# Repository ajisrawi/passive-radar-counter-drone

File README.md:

A **passive radar** that finds small drones without transmitting anything. It listens to the **digital TV, 4G and 5G signals already in the air**. It compares each signal as it arrives straight from the tower with its faint echo off a drone, which gives range, speed and bearing. An on-board FPGA then tells **drones from birds** by their micro-Doppler: spinning rotors make different echo patterns from flapping wings.

- **No transmitter:** no licence needed, nothing to jam, and the radar itself is invisible.
- **Three illuminators at once:** TV towers give long range, and wide 4G/5G channels give fine range resolution.
- **Built end to end:** simulation → custom PCBs → FPGA firmware → antennas → radome → enclosure.

<p align="center">
  
  <br><sub><b>The whole site:</b> one antenna radome (all four bands), two reference antennas pointing at the transmitters, one receiver box</sub>
</p>

---

## Contents

- [How it works](#how-it-works)
- [Simulation results](#simulation-results)
- [Receiver hardware](#receiver-hardware)
- [Firmware: FPGA + ARM](#firmware-fpga--arm)
- [Antennas and radome](#antennas-and-radome)
- [Enclosure](#enclosure)
- [Run it](#run-it)
- [Repository layout](#repository-layout)
- [Status](#status)

---

## How it works

```
   TV / 4G / 5G tower ──────── direct signal ───────────►  reference antenna (LPDA) ─┐
          │                                                                          │
          └──► drone ── faint echo ──►  surveillance array (4 slant dipoles / band) ──┤
                                                                                     ▼
   Board A2  RF front end, 6 ch, LNAs + noise-source calibration (one per band)
        │
   Board B   3 × AD9361 digitizer, 6 coherent channels            ×2 stacks per band
        │
   Board C2  Zynq: cancel the direct signal ─► stream to host ─► detect, track
             └► micro-Doppler engine (8 cued targets) ─► ARM classifier: UAV / bird
```

| Band group | Frequencies | Services | Why |
|---|---|---|---|
| `uhf` | 470–821 MHz | DVB-T, LTE B20/B28, 5G n28 | high-power TV towers give the longest range |
| `mid` | 1805–2170 MHz | LTE B3, B1 | dense cell coverage |
| `high` | 2496–2690 MHz | LTE B7, 5G n41 | wide channels |
| `n78` | 3300–3800 MHz | 5G n78 | 100 MHz channels give the finest range resolution |

The full design, from requirements to link budget, architecture and deployment, is in **[docs/DESIGN.md](docs/DESIGN.md)**.

---

## Simulation results

A Python model of the whole signal-processing chain (`pcl/`) puts a quadcopter, a fixed-wing drone and a bird in a simulated scene.

<p align="center">
  
  <br><sub><b>Range-Doppler map.</b> Left: the direct signal and ground clutter hide everything. Right: after clutter cancellation (ECA) and beamforming, both drones stand out about 25 dB above the noise.</sub>
</p>

<p align="center">
  
  <br><sub><b>Micro-Doppler.</b> The bird's wing beat hugs the body line. The drones show rotor or propeller lines out to ±240 Hz, so they're classified as <b>UAV</b>.</sub>
</p>

<table>
<tr>
<td width="50%"><br><sub><b>Tracking:</b> an EKF tracker over 10 s. Each track is labelled bird or UAV.</sub></td>
<td width="50%"><br><sub><b>Localisation:</b> the bistatic range ellipse crossed with the measured direction of arrival.</sub></td>
</tr>
</table>

---

## Receiver hardware

There are three custom boards per receiver stack, all designed in **OpenSchematic / OpenBoard**. Each band has one A2 front end and two stacks.

<table>
<tr>
<td width="50%"></td>
<td width="50%"></td>
</tr>
<tr>
<td><b>Board C2:</b> Zynq XC7Z035, DDR3, SFP+ 10 GbE, FMC to Board B. 10 layers, 0 DRC errors.</td>
<td><b>Board B:</b> three AD9361 transceivers giving 6 phase-coherent receive channels, with a shared clock and multi-chip sync.</td>
</tr>
<tr>
<td width="50%"></td>
<td width="50%"></td>
</tr>
<tr>
<td><b>Board A2:</b> six-channel RF front end with LNAs, band filters and a noise source that calibrates all channels' phase. Built in four band versions.</td>
<td><b>Board C:</b> Zynq XC7Z020, the lower-cost processor for TV-only stacks.</td>
</tr>
</table>

Schematics, layouts, Gerbers, BOMs and pick-and-place files are in `hardware/board_*/` and `hardware/release/`. See **[hardware/HARDWARE.md](hardware/HARDWARE.md)**.

---

## Firmware: FPGA + ARM

| Block | What it does | Verified |
|---|---|---|
| `canceller.v` | 128-tap complex direct-signal canceller per channel; taps loaded from the host | bit-exact against the Python model, 0 mismatches |
| `md_engine.v` | micro-Doppler engine: beamforms and range-gates up to 8 targets the host is tracking, continuously | 0 mismatches |
| `stream_pack.v` | packs reference + residual into UDP-sized packets | 0 mismatches |
| `ad_merge.v` | aligns the three AD9361 clock domains | 955 samples aligned, no loss |
| `md_classifier.py` (ARM) | Hann spectra → UAV / bird / no signal | false-alarm rate 0.25% |

**End-to-end simulation:** a near quadcopter is classified **UAV** in 4 s and a bird **bird**; the canceller removes 43.6 dB of direct signal. The Board C build uses 67% of the XC7Z020's DSP slices. Details are in **[firmware/FIRMWARE.md](firmware/FIRMWARE.md)**.

---

## Antennas and radome

<table>
<tr>
<td width="50%"></td>
<td width="50%"></td>
</tr>
<tr>
<td><b>One radome, four bands:</b> 4 UHF bowties on top and 3 × 4 printed dipoles below, all tilted +45° to match the cell sites' polarization.</td>
<td><b>The antenna set:</b> the combined radome, plus log-periodic reference antennas for UHF (aluminium) and 1.7–4 GHz (PCB).</td>
</tr>
</table>

<table>
<tr>
<td width="50%"></td>
<td width="50%"></td>
</tr>
<tr>
<td><b>Array patterns:</b> beam steered across ±50°.</td>
<td><b>Radome loss:</b> under 0.45 dB dry in every band; a rain film costs up to 2.9 dB at n78.</td>
</tr>
</table>

<p align="center">

  <br><sub>Antenna PCBs: printed dipoles with a built-in balun, and the printed LPDA. All have fab files.</sub>
</p>

See **[ANTENNA.md](hardware/antenna/ANTENNA.md)** and **[RADOME.md](hardware/antenna/RADOME.md)**.

---

## Enclosure

<table>
<tr>
<td width="50%"></td>
<td width="50%"></td>
</tr>
<tr>
<td><b>Inside:</b> four band columns. Each has its A2 at the bottom and two receiver stacks above. 20 boards, about 158 W.</td>
<td><b>Outside:</b> cast aluminium, IP65, finned cover. Underneath: 24 antenna inputs, one 12-fibre connector and 48 V DC.</td>
</tr>
</table>

See **[ENCLOSURE.md](hardware/enclosure/ENCLOSURE.md)**.

---

## Run it

```bash
pip install -r requirements.txt
python -m pcl.link_budget        # detection-range table
python -m pcl.data_rate          # receiver-to-host data budget
python run_demo.py               # one CPI: detection + localisation -> output/
python run_tracking_demo.py      # 10 s, 3 targets: tracking + drone/bird classification (~5 min)
python firmware/sim/run_tests.py # FPGA HDL vs bit-true models (needs Icarus Verilog)
python firmware/sim/test_e2e.py 4  # scene -> FPGA model -> on-board classifier
```

The Blender models re-render with:

```bash
blender -b -P hardware/antenna/radome_blender.py
blender -b -P hardware/enclosure/enclosure_all_blender.py
```

---

## Repository layout

| Path | Contents |
|---|---|
| `docs/` | design document, images |
| `pcl/` | signal-processing simulation: geometry, signal model, ECA, cross-ambiguity, CFAR, DOA, EKF tracking, micro-Doppler classifier |
| `firmware/hdl/` | Verilog: canceller, micro-Doppler engine, stream packer, AXI core, clock-domain merge |
| `firmware/model/`, `firmware/sim/` | bit-true Python models and testbenches |
| `firmware/ps/` | ARM side: node daemon, classifier, radio control, UDP streamer |
| `firmware/vivado/`, `firmware/linux/` | Vivado block design and pin constraints, Linux device-tree overlay |
| `hardware/board_a2/`, `board_b*/`, `board_c*/` | board designs: schematics, layouts, fab files |
| `hardware/antenna/` | antenna design, PCBs, radome, renders |
| `hardware/enclosure/` | receiver enclosure models and renders |
| `hardware/tools/` | layout, routing, DRC and rendering scripts |

**Not included:** Freerouting and a Java runtime, and the vendor 3D component models (`hardware/lib/prc.3dshapes`). Fetch them separately if needed.

---

## Status

This is a **design and simulation project**. Nothing has been built or tested on real hardware yet, and every RF figure is calculated, not measured.

| Done | Still to do |
|---|---|
| Signal processing simulated end to end | Build and bring up the boards |
| Board layouts at 0 DRC errors, fab files | Vivado build and timing closure |
| FPGA blocks verified bit-exact in simulation | Linux device tree on hardware; C streamer on the board |
| Antenna, radome and enclosure concepts | Antenna tests on a VNA; radome and enclosure CAD |

---

<p align="center">
  <br>
  <sub>© 2026 ajisrawi. All rights reserved. No licence is granted.</sub>
</p>

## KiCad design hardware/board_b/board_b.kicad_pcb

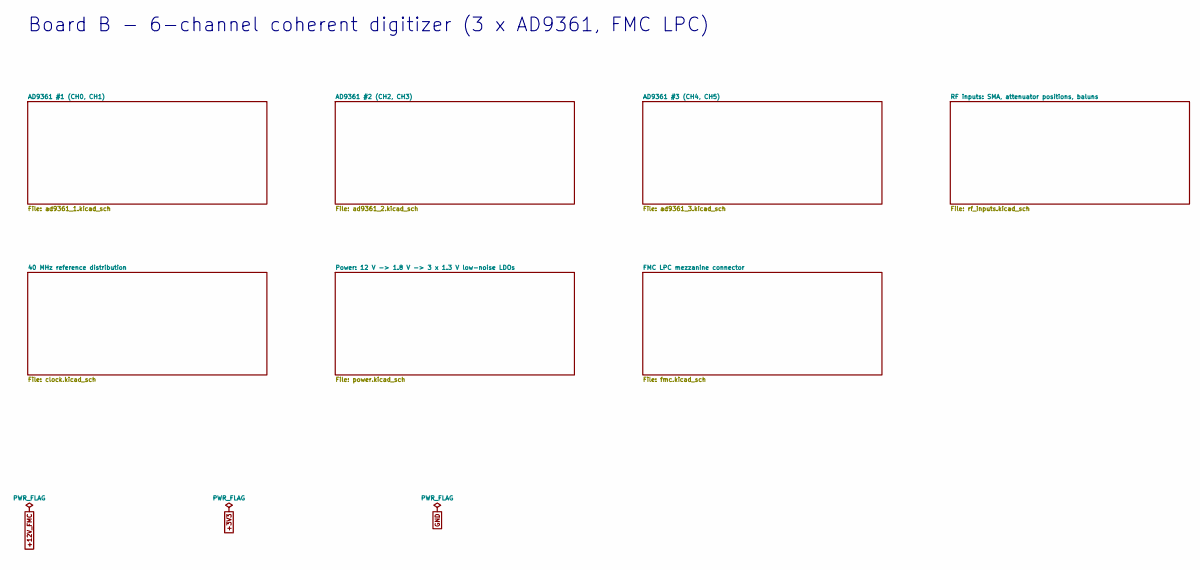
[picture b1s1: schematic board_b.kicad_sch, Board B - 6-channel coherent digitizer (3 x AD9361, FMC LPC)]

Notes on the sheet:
Board B - 6-channel coherent digitizer (3 x AD9361, FMC LPC)

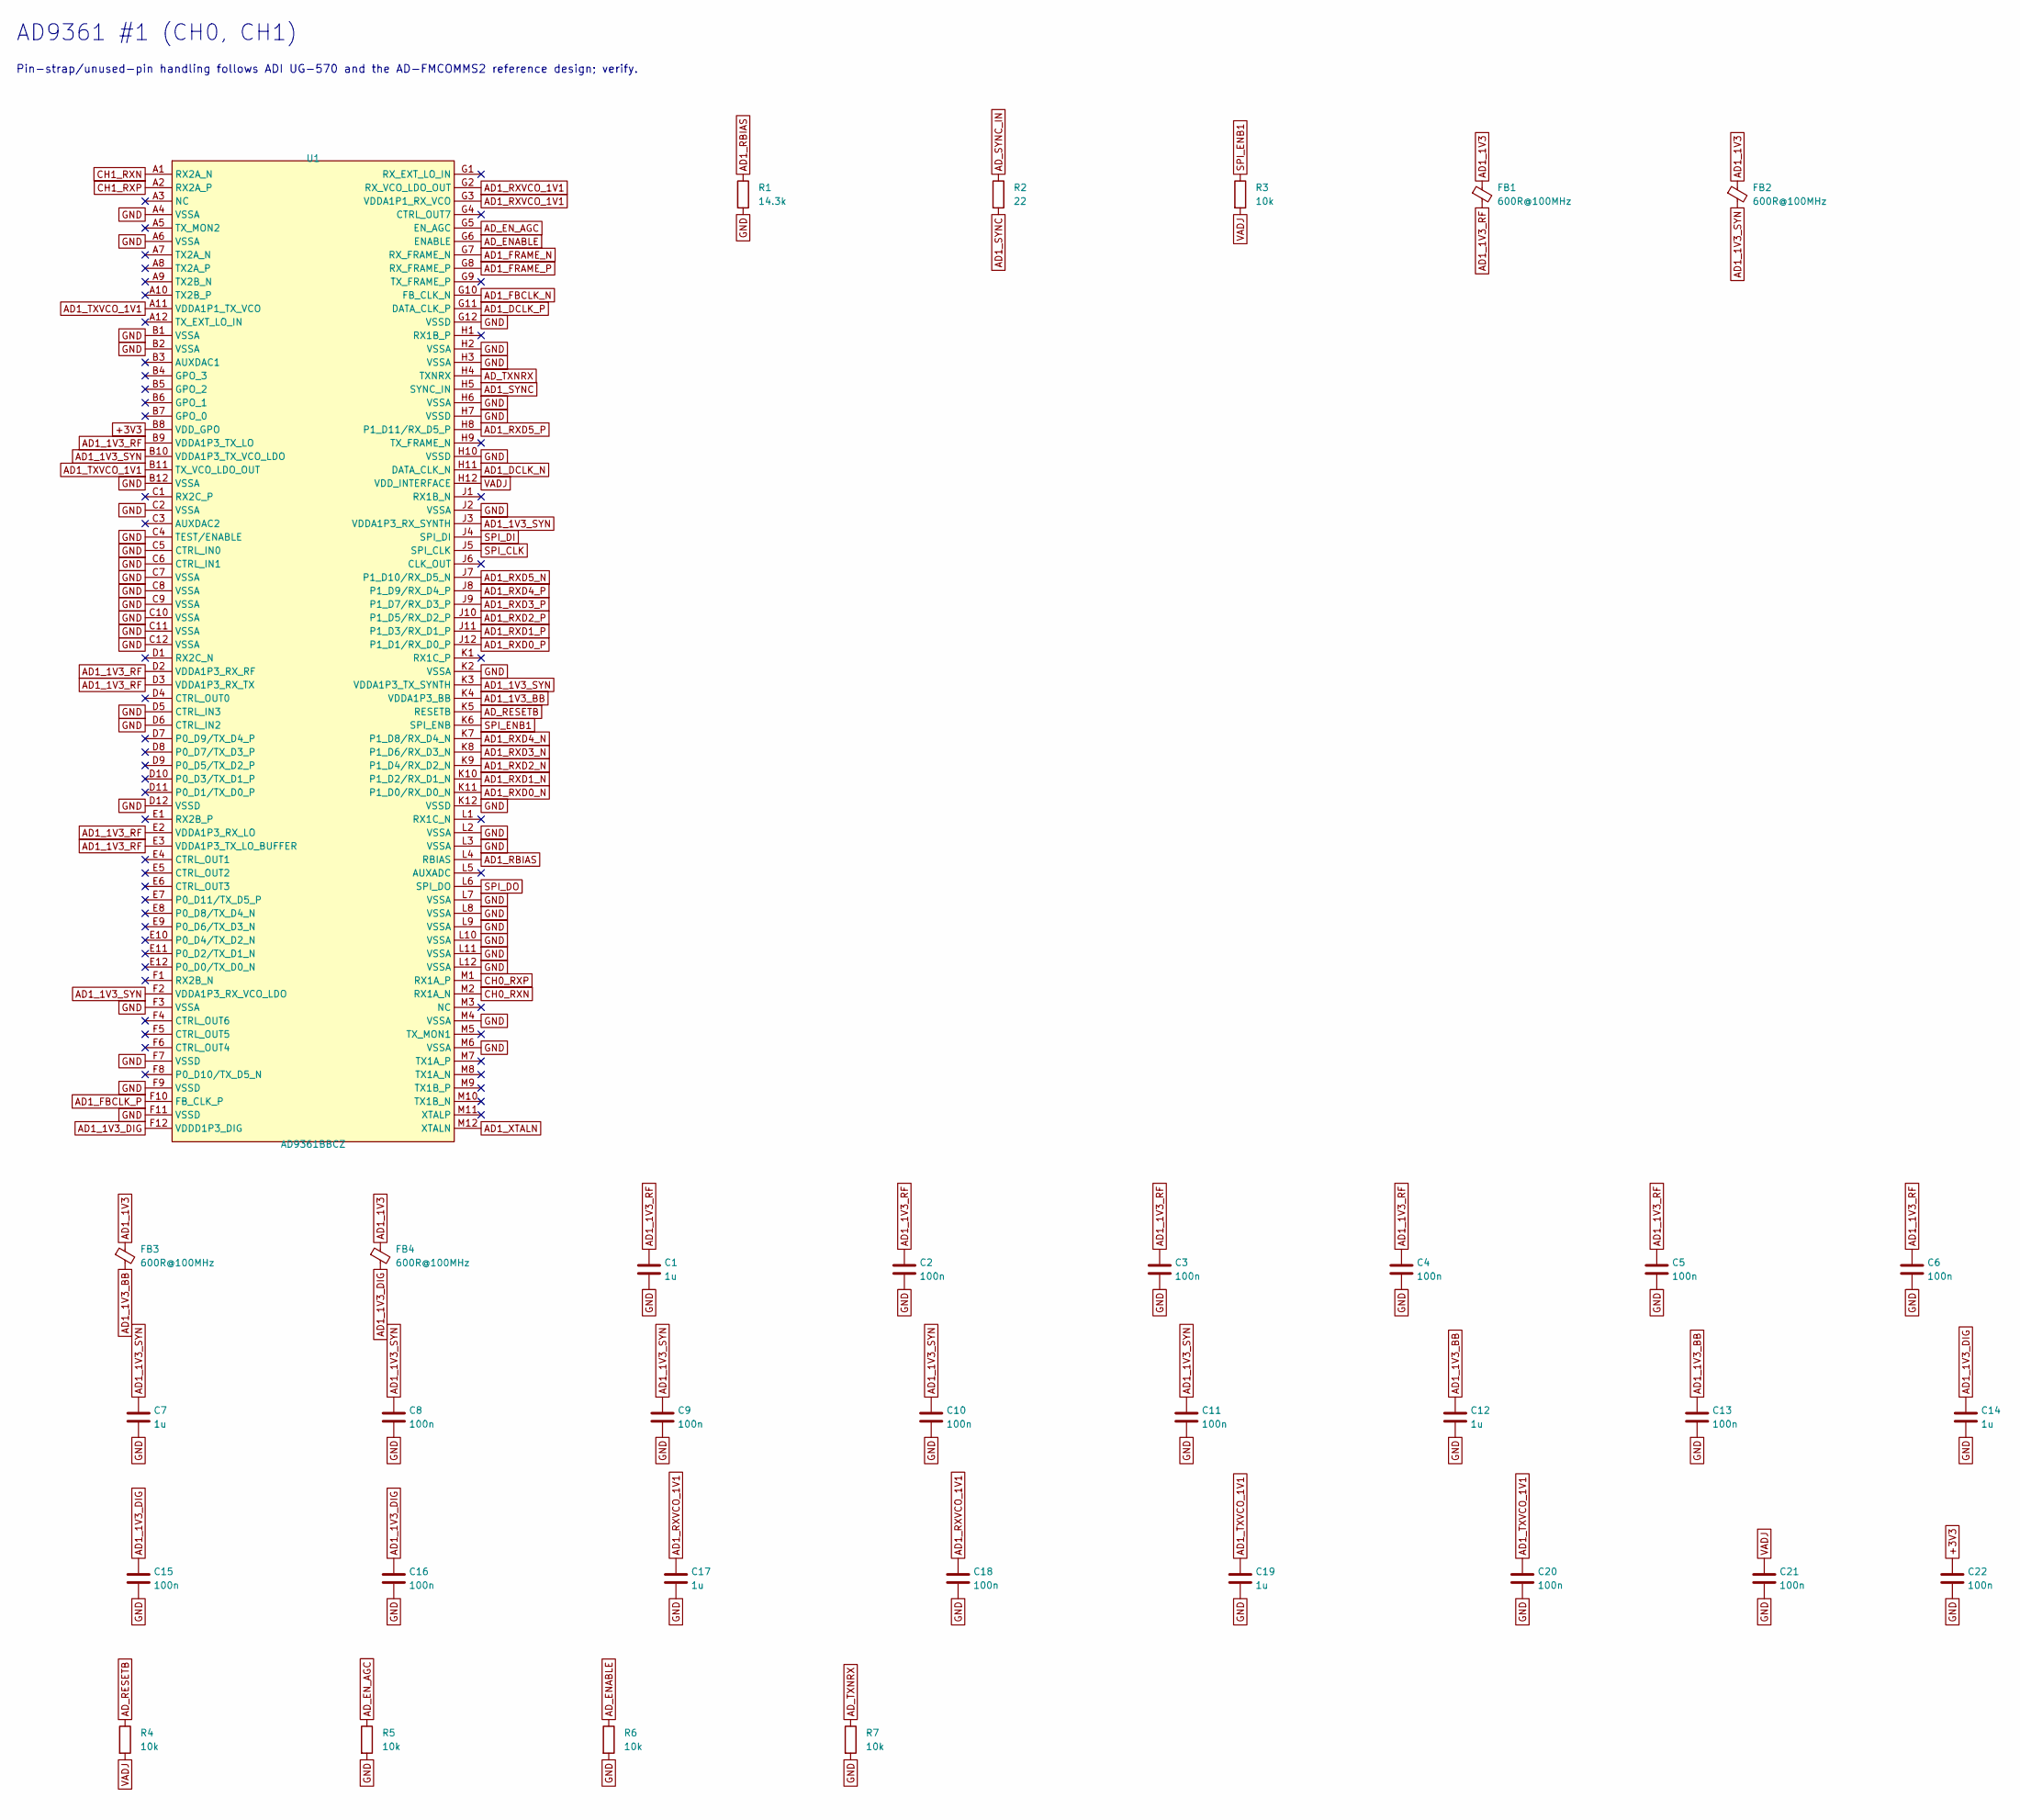
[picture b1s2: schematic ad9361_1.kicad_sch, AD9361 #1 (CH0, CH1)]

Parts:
C1, C7, C12, C14, C17, C19: 1u; C_0402_1005Metric; LCSC C52923
C2, C3, C4, C5, C6, C8, C9, C10, C11, C13, C15, C16, C18, C20, C21, C22: 100n; C_0402_1005Metric; LCSC C1525
FB1, FB2, FB3, FB4: 600R@100MHz; L_0603_1608Metric
R1: 14.3k; R_0402_1005Metric; Tolerance 1%
R2: 22; R_0402_1005Metric
R3, R4, R5, R6, R7: 10k; R_0402_1005Metric; LCSC C25744
U1: AD9361BBCZ; CSPBGA-144_L10.0-W10.0-R12-C12-P0.80-BL; MPN AD9361BBCZ; LCSC C515884

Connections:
+3V3: C22.1, U1.B8 (VDD_GPO); also elsewhere on the board
AD1_1V3: FB1.1, FB2.1, FB3.1, FB4.1; also elsewhere on the board
AD1_1V3_BB: C12.1, C13.1, FB3.2, U1.K4 (VDDA1P3_BB)
AD1_1V3_DIG: C14.1, C15.1, C16.1, FB4.2, U1.F12 (VDDD1P3_DIG)
AD1_1V3_RF: C1.1, C2.1, C3.1, C4.1, C5.1, C6.1, FB1.2, U1.B9 (VDDA1P3_TX_LO), U1.D2 (VDDA1P3_RX_RF), U1.D3 (VDDA1P3_RX_TX), U1.E2 (VDDA1P3_RX_LO), U1.E3 (VDDA1P3_TX_LO_BUFFER)
AD1_1V3_SYN: C7.1, C8.1, C9.1, C10.1, C11.1, FB2.2, U1.B10 (VDDA1P3_TX_VCO_LDO), U1.F2 (VDDA1P3_RX_VCO_LDO), U1.J3 (VDDA1P3_RX_SYNTH), U1.K3 (VDDA1P3_TX_SYNTH)
AD1_DCLK_N: U1.H11 (DATA_CLK_N); also elsewhere on the board
AD1_DCLK_P: U1.G11 (DATA_CLK_P); also elsewhere on the board
AD1_FBCLK_N: U1.G10 (FB_CLK_N); also elsewhere on the board
AD1_FBCLK_P: U1.F10 (FB_CLK_P); also elsewhere on the board
AD1_FRAME_N: U1.G7 (RX_FRAME_N); also elsewhere on the board
AD1_FRAME_P: U1.G8 (RX_FRAME_P); also elsewhere on the board
AD1_RBIAS: R1.1, U1.L4 (RBIAS)
AD1_RXD0_N: U1.K11 (P1_D0/RX_D0_N); also elsewhere on the board
AD1_RXD0_P: U1.J12 (P1_D1/RX_D0_P); also elsewhere on the board
AD1_RXD1_N: U1.K10 (P1_D2/RX_D1_N); also elsewhere on the board
AD1_RXD1_P: U1.J11 (P1_D3/RX_D1_P); also elsewhere on the board
AD1_RXD2_N: U1.K9 (P1_D4/RX_D2_N); also elsewhere on the board
AD1_RXD2_P: U1.J10 (P1_D5/RX_D2_P); also elsewhere on the board
AD1_RXD3_N: U1.K8 (P1_D6/RX_D3_N); also elsewhere on the board
AD1_RXD3_P: U1.J9 (P1_D7/RX_D3_P); also elsewhere on the board
AD1_RXD4_N: U1.K7 (P1_D8/RX_D4_N); also elsewhere on the board
AD1_RXD4_P: U1.J8 (P1_D9/RX_D4_P); also elsewhere on the board
AD1_RXD5_N: U1.J7 (P1_D10/RX_D5_N); also elsewhere on the board
AD1_RXD5_P: U1.H8 (P1_D11/RX_D5_P); also elsewhere on the board
AD1_RXVCO_1V1: C17.1, C18.1, U1.G2 (RX_VCO_LDO_OUT), U1.G3 (VDDA1P1_RX_VCO)
AD1_SYNC: R2.2, U1.H5 (SYNC_IN)
AD1_TXVCO_1V1: C19.1, C20.1, U1.A11 (VDDA1P1_TX_VCO), U1.B11 (TX_VCO_LDO_OUT)
AD1_XTALN: U1.M12 (XTALN); also elsewhere on the board
AD_ENABLE: R6.1, U1.G6 (ENABLE); also elsewhere on the board
AD_EN_AGC: R5.1, U1.G5 (EN_AGC); also elsewhere on the board
AD_RESETB: R4.1, U1.K5 (RESETB); also elsewhere on the board
AD_SYNC_IN: R2.1; also elsewhere on the board
AD_TXNRX: R7.1, U1.H4 (TXNRX); also elsewhere on the board
CH0_RXN: U1.M2 (RX1A_N); also elsewhere on the board
CH0_RXP: U1.M1 (RX1A_P); also elsewhere on the board
CH1_RXN: U1.A1 (RX2A_N); also elsewhere on the board
CH1_RXP: U1.A2 (RX2A_P); also elsewhere on the board
GND: C1.2, C2.2, C3.2, C4.2, C5.2, C6.2, C7.2, C8.2, C9.2, C10.2, C11.2, C12.2, C13.2, C14.2, C15.2, C16.2, C17.2, C18.2, C19.2, C20.2, C21.2, C22.2, R1.2, R5.2, R6.2, R7.2, U1.A4 (VSSA), U1.A6 (VSSA), U1.B1 (VSSA), U1.B2 (VSSA), U1.B12 (VSSA), U1.C2 (VSSA), U1.C4 (TEST/ENABLE), U1.C5 (CTRL_IN0), U1.C6 (CTRL_IN1), U1.C7 (VSSA), U1.C8 (VSSA), U1.C9 (VSSA), U1.C10 (VSSA), U1.C11 (VSSA), U1.C12 (VSSA), U1.D5 (CTRL_IN3), U1.D6 (CTRL_IN2), U1.D12 (VSSD), U1.F3 (VSSA), U1.F7 (VSSD), U1.F9 (VSSD), U1.F11 (VSSD), U1.G12 (VSSD), U1.H2 (VSSA), U1.H3 (VSSA), U1.H6 (VSSA), U1.H7 (VSSD), U1.H10 (VSSD), U1.J2 (VSSA), U1.K2 (VSSA), U1.K12 (VSSD), U1.L2 (VSSA), U1.L3 (VSSA), U1.L7 (VSSA), U1.L8 (VSSA), U1.L9 (VSSA), U1.L10 (VSSA), U1.L11 (VSSA), U1.L12 (VSSA), U1.M4 (VSSA), U1.M6 (VSSA); also elsewhere on the board
SPI_CLK: U1.J5 (SPI_CLK); also elsewhere on the board
SPI_DI: U1.J4 (SPI_DI); also elsewhere on the board
SPI_DO: U1.L6 (SPI_DO); also elsewhere on the board
SPI_ENB1: R3.1, U1.K6 (SPI_ENB); also elsewhere on the board
VADJ: C21.1, R3.2, R4.2, U1.H12 (VDD_INTERFACE); also elsewhere on the board

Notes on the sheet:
AD9361 #1 (CH0, CH1)
Pin-strap/unused-pin handling follows ADI UG-570 and the AD-FMCOMMS2 reference design; verify.

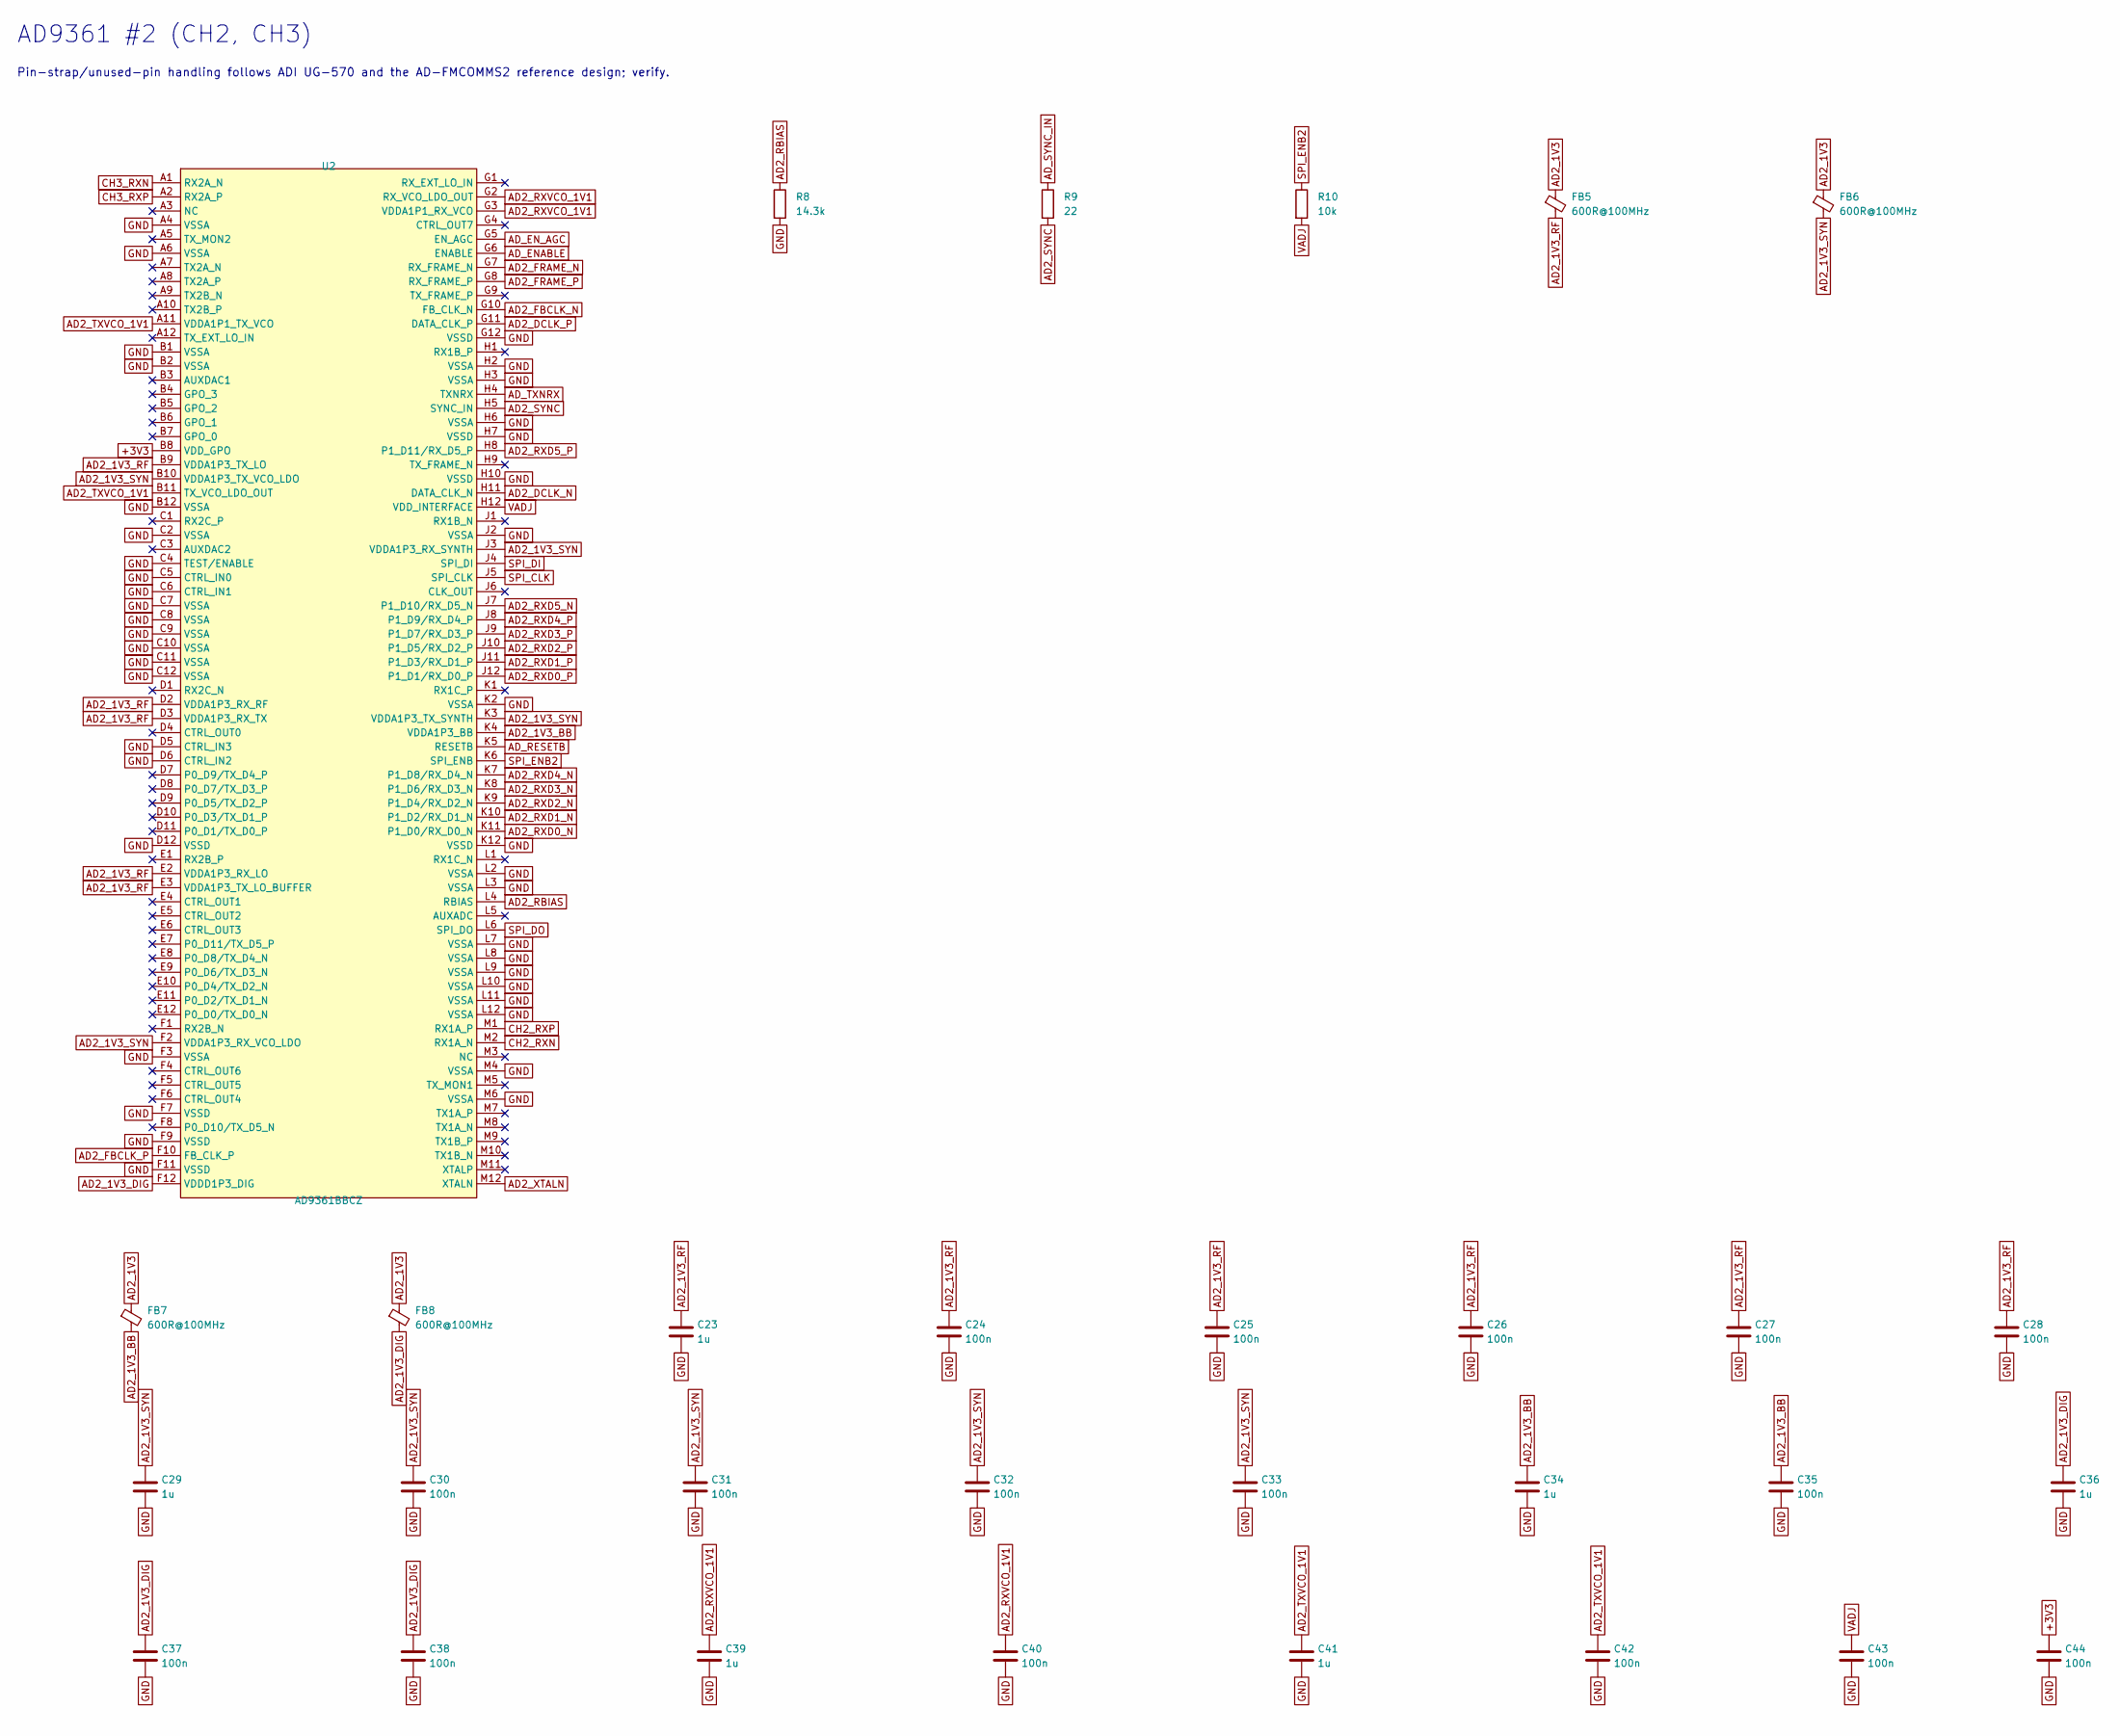
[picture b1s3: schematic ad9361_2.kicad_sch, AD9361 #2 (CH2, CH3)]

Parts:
C23, C29, C34, C36, C39, C41: 1u; C_0402_1005Metric; LCSC C52923
C24, C25, C26, C27, C28, C30, C31, C32, C33, C35, C37, C38, C40, C42, C43, C44: 100n; C_0402_1005Metric; LCSC C1525
FB5, FB6, FB7, FB8: 600R@100MHz; L_0603_1608Metric
R8: 14.3k; R_0402_1005Metric; Tolerance 1%
R9: 22; R_0402_1005Metric
R10: 10k; R_0402_1005Metric; LCSC C25744
U2: AD9361BBCZ; CSPBGA-144_L10.0-W10.0-R12-C12-P0.80-BL; MPN AD9361BBCZ; LCSC C515884

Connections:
+3V3: C44.1, U2.B8 (VDD_GPO); also elsewhere on the board
AD2_1V3: FB5.1, FB6.1, FB7.1, FB8.1; also elsewhere on the board
AD2_1V3_BB: C34.1, C35.1, FB7.2, U2.K4 (VDDA1P3_BB)
AD2_1V3_DIG: C36.1, C37.1, C38.1, FB8.2, U2.F12 (VDDD1P3_DIG)
AD2_1V3_RF: C23.1, C24.1, C25.1, C26.1, C27.1, C28.1, FB5.2, U2.B9 (VDDA1P3_TX_LO), U2.D2 (VDDA1P3_RX_RF), U2.D3 (VDDA1P3_RX_TX), U2.E2 (VDDA1P3_RX_LO), U2.E3 (VDDA1P3_TX_LO_BUFFER)
AD2_1V3_SYN: C29.1, C30.1, C31.1, C32.1, C33.1, FB6.2, U2.B10 (VDDA1P3_TX_VCO_LDO), U2.F2 (VDDA1P3_RX_VCO_LDO), U2.J3 (VDDA1P3_RX_SYNTH), U2.K3 (VDDA1P3_TX_SYNTH)
AD2_DCLK_N: U2.H11 (DATA_CLK_N); also elsewhere on the board
AD2_DCLK_P: U2.G11 (DATA_CLK_P); also elsewhere on the board
AD2_FBCLK_N: U2.G10 (FB_CLK_N); also elsewhere on the board
AD2_FBCLK_P: U2.F10 (FB_CLK_P); also elsewhere on the board
AD2_FRAME_N: U2.G7 (RX_FRAME_N); also elsewhere on the board
AD2_FRAME_P: U2.G8 (RX_FRAME_P); also elsewhere on the board
AD2_RBIAS: R8.1, U2.L4 (RBIAS)
AD2_RXD0_N: U2.K11 (P1_D0/RX_D0_N); also elsewhere on the board
AD2_RXD0_P: U2.J12 (P1_D1/RX_D0_P); also elsewhere on the board
AD2_RXD1_N: U2.K10 (P1_D2/RX_D1_N); also elsewhere on the board
AD2_RXD1_P: U2.J11 (P1_D3/RX_D1_P); also elsewhere on the board
AD2_RXD2_N: U2.K9 (P1_D4/RX_D2_N); also elsewhere on the board
AD2_RXD2_P: U2.J10 (P1_D5/RX_D2_P); also elsewhere on the board
AD2_RXD3_N: U2.K8 (P1_D6/RX_D3_N); also elsewhere on the board
AD2_RXD3_P: U2.J9 (P1_D7/RX_D3_P); also elsewhere on the board
AD2_RXD4_N: U2.K7 (P1_D8/RX_D4_N); also elsewhere on the board
AD2_RXD4_P: U2.J8 (P1_D9/RX_D4_P); also elsewhere on the board
AD2_RXD5_N: U2.J7 (P1_D10/RX_D5_N); also elsewhere on the board
AD2_RXD5_P: U2.H8 (P1_D11/RX_D5_P); also elsewhere on the board
AD2_RXVCO_1V1: C39.1, C40.1, U2.G2 (RX_VCO_LDO_OUT), U2.G3 (VDDA1P1_RX_VCO)
AD2_SYNC: R9.2, U2.H5 (SYNC_IN)
AD2_TXVCO_1V1: C41.1, C42.1, U2.A11 (VDDA1P1_TX_VCO), U2.B11 (TX_VCO_LDO_OUT)
AD2_XTALN: U2.M12 (XTALN); also elsewhere on the board
AD_ENABLE: U2.G6 (ENABLE); also elsewhere on the board
AD_EN_AGC: U2.G5 (EN_AGC); also elsewhere on the board
AD_RESETB: U2.K5 (RESETB); also elsewhere on the board
AD_SYNC_IN: R9.1; also elsewhere on the board
AD_TXNRX: U2.H4 (TXNRX); also elsewhere on the board
CH2_RXN: U2.M2 (RX1A_N); also elsewhere on the board
CH2_RXP: U2.M1 (RX1A_P); also elsewhere on the board
CH3_RXN: U2.A1 (RX2A_N); also elsewhere on the board
CH3_RXP: U2.A2 (RX2A_P); also elsewhere on the board
GND: C23.2, C24.2, C25.2, C26.2, C27.2, C28.2, C29.2, C30.2, C31.2, C32.2, C33.2, C34.2, C35.2, C36.2, C37.2, C38.2, C39.2, C40.2, C41.2, C42.2, C43.2, C44.2, R8.2, U2.A4 (VSSA), U2.A6 (VSSA), U2.B1 (VSSA), U2.B2 (VSSA), U2.B12 (VSSA), U2.C2 (VSSA), U2.C4 (TEST/ENABLE), U2.C5 (CTRL_IN0), U2.C6 (CTRL_IN1), U2.C7 (VSSA), U2.C8 (VSSA), U2.C9 (VSSA), U2.C10 (VSSA), U2.C11 (VSSA), U2.C12 (VSSA), U2.D5 (CTRL_IN3), U2.D6 (CTRL_IN2), U2.D12 (VSSD), U2.F3 (VSSA), U2.F7 (VSSD), U2.F9 (VSSD), U2.F11 (VSSD), U2.G12 (VSSD), U2.H2 (VSSA), U2.H3 (VSSA), U2.H6 (VSSA), U2.H7 (VSSD), U2.H10 (VSSD), U2.J2 (VSSA), U2.K2 (VSSA), U2.K12 (VSSD), U2.L2 (VSSA), U2.L3 (VSSA), U2.L7 (VSSA), U2.L8 (VSSA), U2.L9 (VSSA), U2.L10 (VSSA), U2.L11 (VSSA), U2.L12 (VSSA), U2.M4 (VSSA), U2.M6 (VSSA); also elsewhere on the board
SPI_CLK: U2.J5 (SPI_CLK); also elsewhere on the board
SPI_DI: U2.J4 (SPI_DI); also elsewhere on the board
SPI_DO: U2.L6 (SPI_DO); also elsewhere on the board
SPI_ENB2: R10.1, U2.K6 (SPI_ENB); also elsewhere on the board
VADJ: C43.1, R10.2, U2.H12 (VDD_INTERFACE); also elsewhere on the board

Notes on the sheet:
AD9361 #2 (CH2, CH3)
Pin-strap/unused-pin handling follows ADI UG-570 and the AD-FMCOMMS2 reference design; verify.

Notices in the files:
README.md:
License: all rights reserved
